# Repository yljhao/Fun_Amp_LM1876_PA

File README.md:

Fun_Amp_LM1876_PA
=================

LM1876TF base parallel power amplifier. Design by KiCad EDA.

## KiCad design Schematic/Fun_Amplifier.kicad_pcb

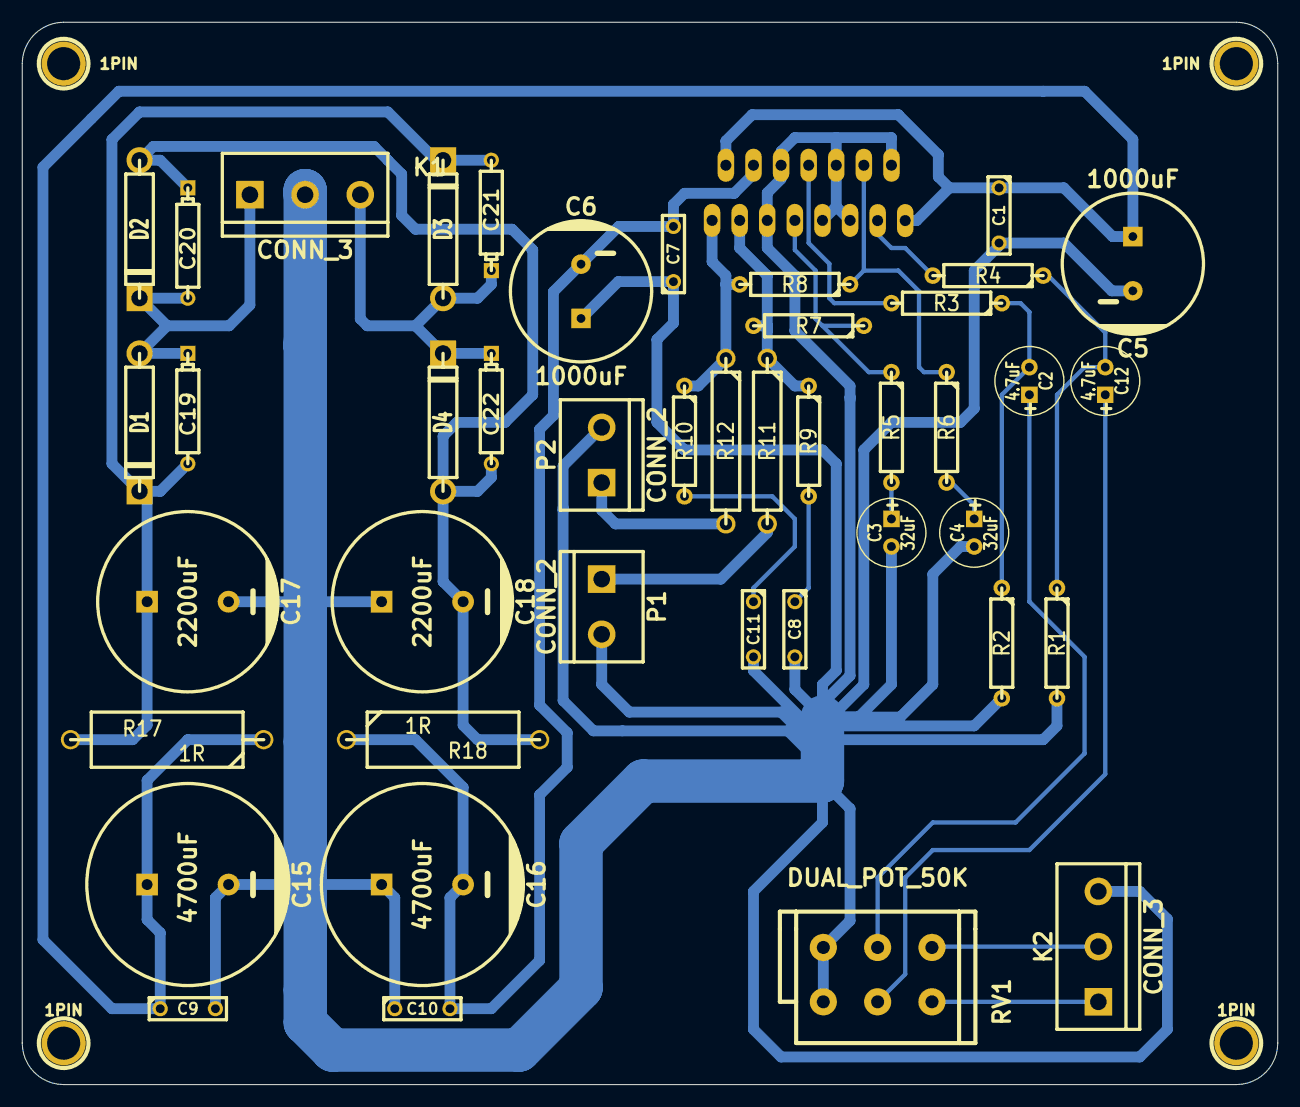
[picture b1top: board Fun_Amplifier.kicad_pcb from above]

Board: 2 copper layers, 115.6 x 97.8 mm, 48 parts (0 on the bottom side), 25 nets.

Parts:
1PIN, 1PIN#2, 1PIN#3, 1PIN#4: P***; 1pin
C1, C7, C8, C9, C10, C11: 0.1uF; C2
C2, C12: 4.7uF; C1V7
C3, C4: 32uF; C1V7
C5, C6: 1000uF; CP_12.5x25mm
C15, C16: 4700uF; CP_18x35.5mm
C17, C18: 2200uF; CP_16x25mm
C19, C20, C21, C22: 10nF; CP4
D1, D2, D3, D4: DIODE; D5_bigdip
K1, K2: CONN_3; bornier3
P1, P2: CONN_2; bornier2
R1, R2, R7, R8: 22K; R4
R3, R4, R5, R6: 680R; R4
R9, R10: 4.7R; R4
R11, R12: 0.1R; R6
R17, R18: 1R; R7
RV1: DUAL_POT_50K; Potentiometer_Alps-RK16-double_RevA_30July2010
U1: LM1876; LM1876TF

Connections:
GND: C1.2, C3.2, C4.2, C5.2, C6.1, C7.1, C8.2, C9.2, C10.1, C11.2, C15.2, C16.1, C17.2, C18.1, K1.2, K2.3, P1.2, P2.2, R1.2, R2.2, RV1.3, RV1.6, U1.5, U1.6, U1.9, U1.10, U1.11, U1.14
unnamed: C12.2, R1.1, R4.1
unnamed: C12.1, RV1.2
unnamed: C2.1, RV1.5
unnamed: K2.1, RV1.1
unnamed: K2.2, RV1.4
unnamed: R7.2, R9.1, R11.1, U1.3
unnamed: R3.2, U1.8
unnamed: R5.1, R7.1, U1.7
unnamed: C3.1, R5.2
unnamed: C8.1, R9.2
unnamed: P1.1, R11.2
unnamed: C17.1, C19.2, C21.2, D1.2, D3.2, R17.2
unnamed: P2.1, R12.2
unnamed: C21.1, C22.1, D3.1, D4.2, K1.3
unnamed: C19.1, C20.2, D1.1, D2.2, K1.1
unnamed: C18.2, C20.1, C22.2, D2.1, D4.1, R18.2
unnamed: C4.1, R6.2
unnamed: R6.1, R8.1, U1.12
unnamed: R4.2, U1.13
unnamed: C11.1, R10.2
unnamed: C2.2, R2.1, R3.1
unnamed: R8.2, R10.1, R12.1, U1.1
VDD: C1.1, C5.1, C9.1, C15.1, R17.1, U1.2, U1.15
VEE: C6.2, C7.2, C10.2, C16.2, R18.1, U1.4

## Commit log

2014-06-29 Initial Commit.
2014-08-26 Commit for... 1. Commit parallel Amplifier circuit.
2014-09-01 Commit for... 1. PCB testing success.
2014-09-19 Amp version 2 with crc regulator and volume control circuit.
